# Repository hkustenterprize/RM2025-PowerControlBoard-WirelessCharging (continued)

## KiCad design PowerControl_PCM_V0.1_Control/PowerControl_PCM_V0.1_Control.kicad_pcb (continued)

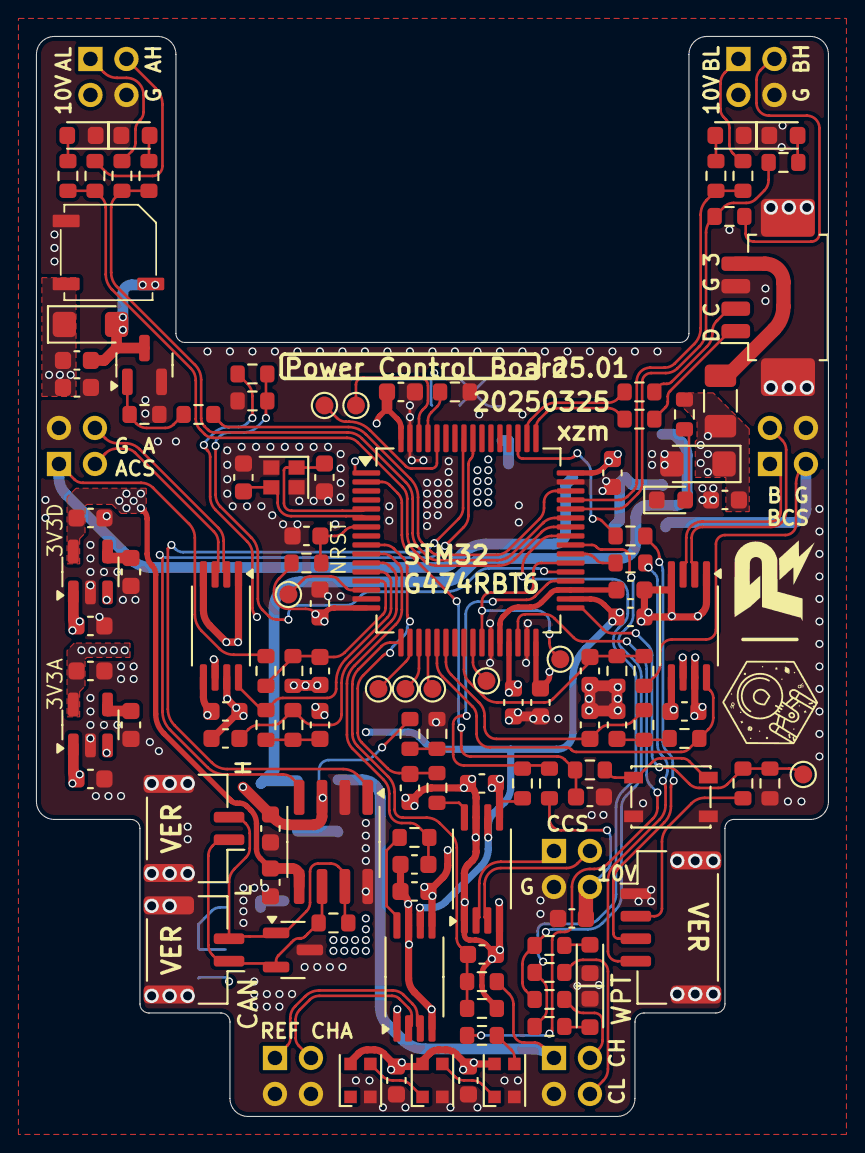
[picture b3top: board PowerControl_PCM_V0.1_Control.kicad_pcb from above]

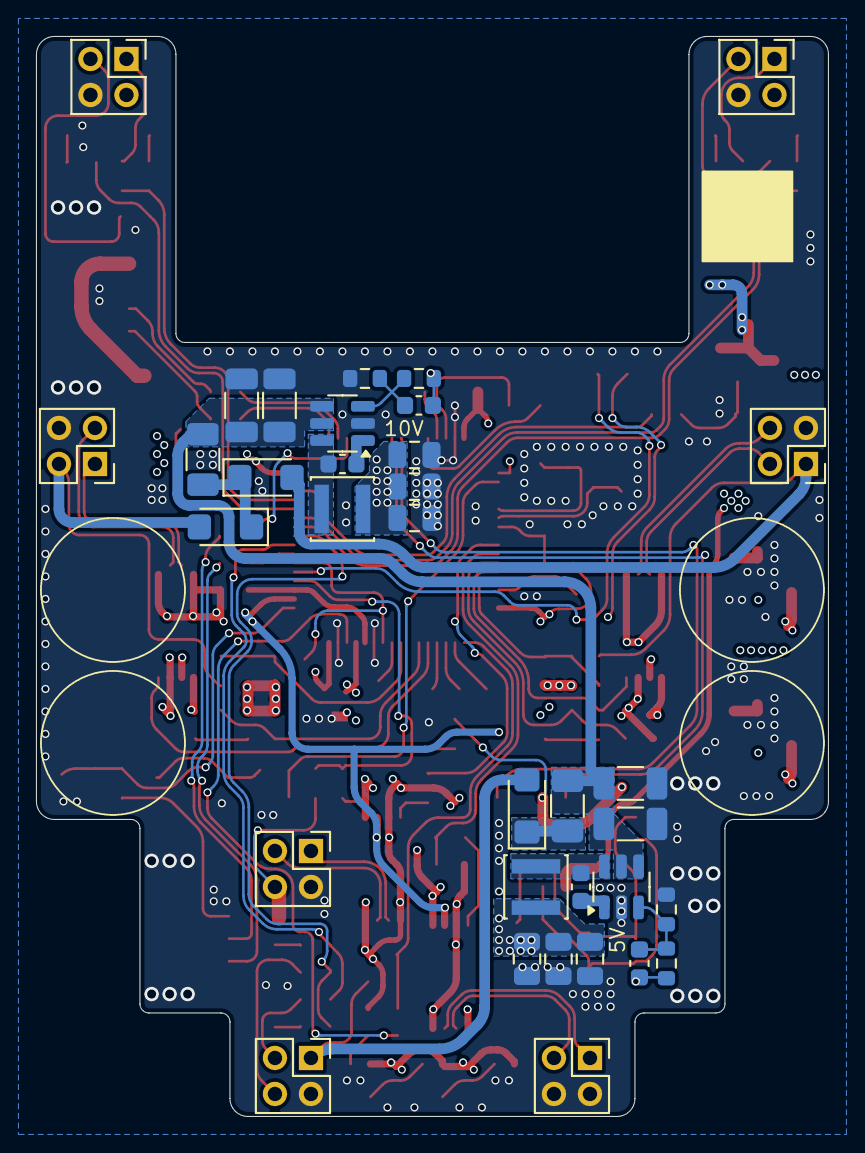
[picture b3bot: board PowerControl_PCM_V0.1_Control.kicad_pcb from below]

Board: 4 copper layers, 44.0 x 60.0 mm, 155 parts (34 on the bottom side), 100 nets.

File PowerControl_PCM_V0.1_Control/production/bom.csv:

Designator,Footprint,Quantity,Value,LCSC Part #
BZ2,Buzzer_5020,1,Buzzer_5020,
"C1, C2, C32, C33, C43, C44, C45, C47, C9",0603,9,3n3,
"C10, C29, C34, C35, C39, C40, C41, C62, C63, C64, C65, C66, C72, C73, C87, C88, C96",0603,17,100n,
"C36, C37, C38, C42, C46, C79",0805,6,22u,
"C48, C49, C50, C74, C85, C86, C90, C94, C95",0603,9,4u7,
"C67, C68, C69, C70",1206,4,10u,
"C75, C77, C78, C89, C91",0603,5,20p,
"C92, C93",0603,2,10n,
D12,SOT-23,1,ESD1CAN,
"D13, D14, D27",WS2812B-2020,3,WS2812B-2020,
D15,0603,1,3V3,
"D18, D21, D7, D8",D_SMF,4,K34,
D19,0603,1,EH,
D20,D_SMF,1,SMF3V3A,
D22,0603,1,AH,
D23,0603,1,AL,
D24,0603,1,BH,
D25,0603,1,BL,
D26,0603,1,EL,
"F4, F5, F6",1206,3,1A 1206,
J1,Molex_PicoBlade_53261-0471_1x04-1MP_P1.25mm_Horizontal,1,SWD,
"J10, J11, J17, J18, J19, J8, J9",PinSocket_2x02_P2.00mm,7,Conn_F,
"J20, J21",JST_GH_BM02B-GHS-TBT_1x02-1MP_P1.25mm_Vertical,2,CAN3,
J22,JST_GH_BM04B-GHS-TBT_1x04-1MP_P1.25mm_Vertical,1,Conn_01x04_MountingPin,
"L1, L4",L_Sunlord_SWPA3015S,2,4u7,
Q11,SOT-23,1,SI2300,
"R1, R40, R43, R45, R47, R48, R49, R50, R51",0603,9,10k,
"R15, R16, R17, R18, R19, R20, R25, R26, R27, R32, R33, R58, R59, R60, R61, R64",0603,16,2k2,
"R21, R28, R29, R30, R31, R39, R41, R46, R52, R53, R54, R55, R57, R62",0603,14,120R,
"R22, R23, R24, R63",0603,4,33k,
"R36, R56",0603,2,1k,
R42,0603,1,118k,
R44,0603,1,53k6,
SW3,Button_PTS810,1,BTN,
TH1,0603,1,Thermistor_NTC,
"TP1, TP2, TP3, TP4, TP5, TP6, TP7, TP8, TP9",TestPoint_Pad_D1.0mm,9,TestPoint,
U12,LQFP-64_10x10mm_P0.5mm,1,STM32G474RBTx,
"U13, U14",SOT-23-6,2,RY8411,
"U16, U17",SOT-23-5,2,RS3236,
"U4, U6, U7, U8",TSSOP-8_4.4x3mm_P0.65mm,4,INA240A1PW,
U5,SOIC-8_3.9x4.9mm_P1.27mm,1,TJA1042T-3,
Y1,Crystal_SMD_2016,1,25Mhz_2016,

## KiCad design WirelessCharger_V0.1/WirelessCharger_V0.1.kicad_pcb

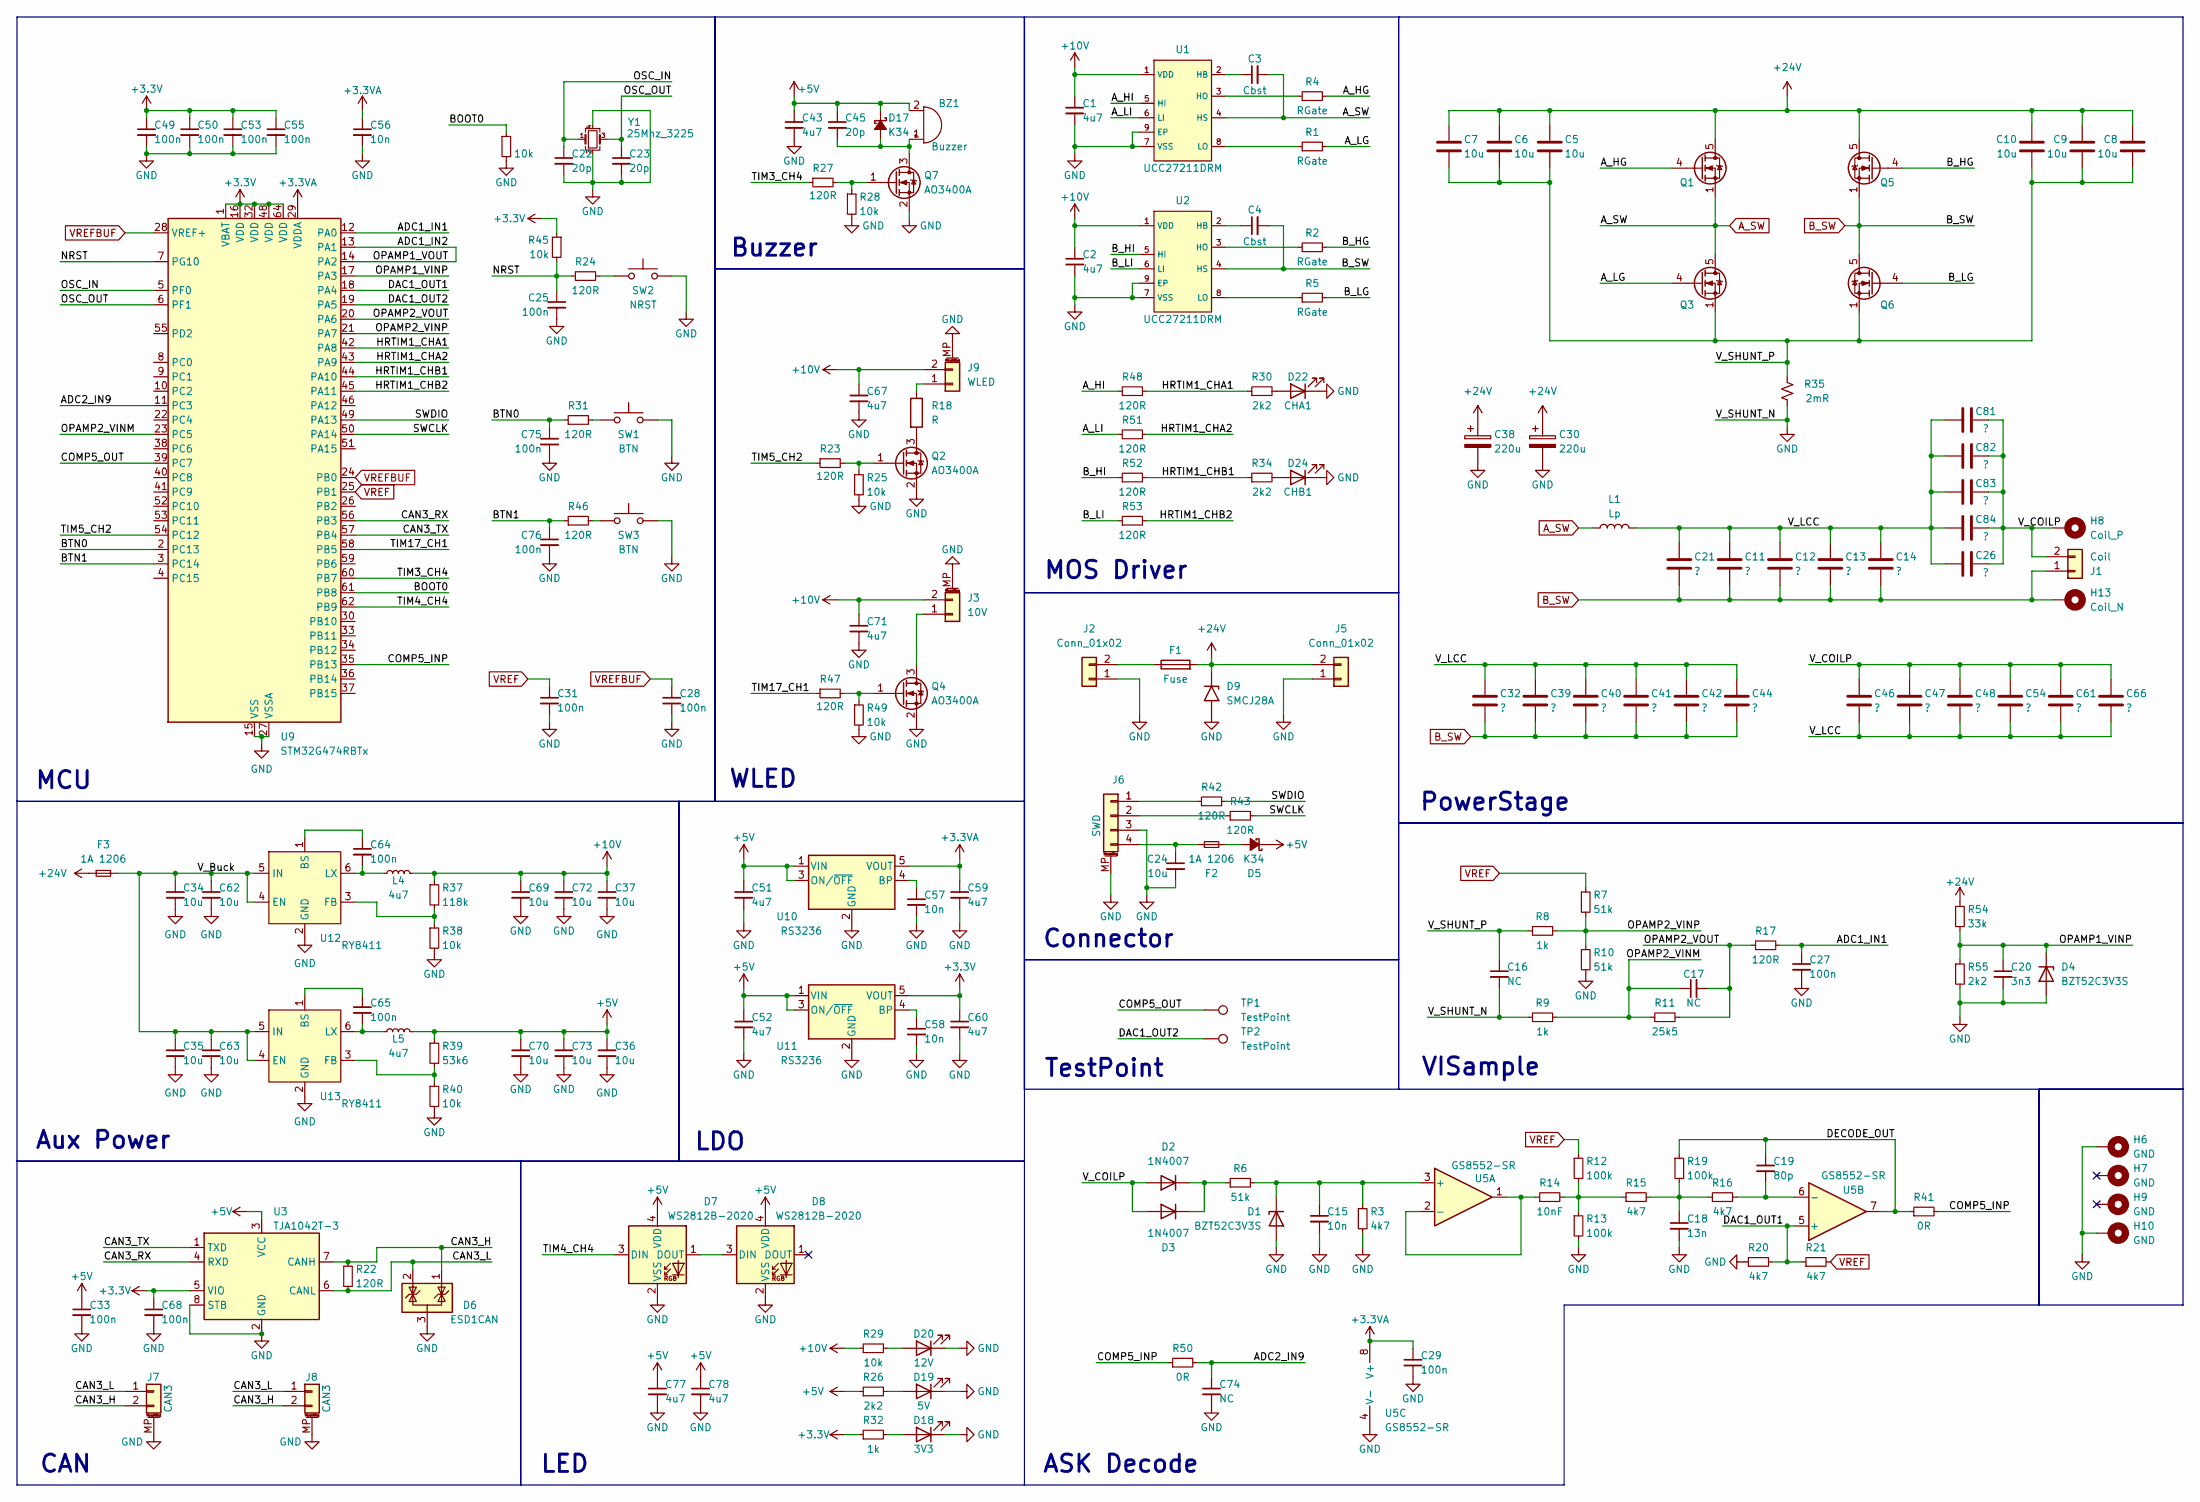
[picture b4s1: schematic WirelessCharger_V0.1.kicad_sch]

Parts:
BZ1: Buzzer; MLT-9032
C1, C2, C43, C51, C52, C59, C60, C67, C71, C77, C78: 4u7; C_0603_1608Metric
C3, C4: Cbst; C_0603_1608Metric
C5, C6, C7, C8, C9, C10, C34, C35, C62, C63: 10u; C_1206_3216Metric
C11, C12, C13, C14, C21, C26, C81, C82, C83, C84: ?; C_Rect_L11.0mm_W5.1mm_P10.00mm_MKT
C15, C56, C57, C58: 10n; C_0603_1608Metric
C16, C17, C74: NC; C_0603_1608Metric
C18: 13n; C_0603_1608Metric
C19: 80p; C_0603_1608Metric
C20: 3n3; C_0603_1608Metric
C22, C23, C45: 20p; C_0603_1608Metric
C24: 10u; C_0603_1608Metric
C25, C27, C28, C29, C31, C33, C49, C50, C53, C55, C64, C65, C68, C75, C76: 100n; C_0603_1608Metric
C30, C38: 220u; CP_Radial_D8.0mm_P3.50mm
C32, C39, C40, C41, C42, C44, C46, C47, C48, C54, C61, C66: ?; C_1206_3216Metric
C36, C37, C69, C70, C72, C73: 10u; C_0805_2012Metric
D1, D4: BZT52C3V3S; D_SOD-123F
D2, D3: 1N4007; D_SMF
D5, D17: K34; D_SMF
D6: ESD1CAN; SOT-23
D7, D8: WS2812B-2020
D9: SMCJ28A; D_SMC
D18: 3V3; LED_0603_1608Metric
D19: 5V; LED_0603_1608Metric
D20: 12V; LED_0603_1608Metric
D22: CHA1; LED_0603_1608Metric
D24: CHB1; LED_0603_1608Metric
F1: Fuse; Fuse_Littelfuse-NANO2-451_453
F2, F3: 1A 1206; Fuse_1206_3216Metric
H6, H7, H9, H10: GND; MountingHole_3.2mm_M3_DIN965_Pad
H8: Coil_P; TestPoint_Plated_Hole_D2.0mm
H13: Coil_N; TestPoint_Plated_Hole_D2.0mm
J1: Coil; AMASS_XT30U-F_Vertical
J2: Conn_01x02; AMASS_XT30U-M_Vertical
J3: 10V; JST_PH_B2B-PH-SM4-TB_1x02-1MP_P2.00mm_Vertical
J5: Conn_01x02; AMASS_XT30U-F_Vertical
J6: SWD; Molex_PicoBlade_53261-0471_1x04-1MP_P1.25mm_Horizontal
J7, J8: CAN3; JST_GH_BM02B-GHS-TBT_1x02-1MP_P1.25mm_Vertical
J9: WLED; JST_PH_B2B-PH-SM4-TB_1x02-1MP_P2.00mm_Vertical
L1: Lp; L_90125_3P
L4, L5: 4u7; L_Sunlord_SWPA3015S
Q1, Q3, Q5, Q6: BSC070N10NS3G; TDSON-8-1
Q2, Q4, Q7: AO3400A; SOT-23
R1, R2, R4, R5: RGate; R_0603_1608Metric
R3, R15, R16, R20, R21: 4k7; R_0603_1608Metric
R6, R7, R10: 51k; R_0603_1608Metric
R8, R9, R32: 1k; R_0603_1608Metric
R11: 25k5; R_0603_1608Metric
R12, R13, R19: 100k; R_0603_1608Metric
R14: 10nF; R_0603_1608Metric
R17, R22, R23, R24, R27, R31, R42, R43, R46, R47, R48, R51, R52, R53: 120R; R_0603_1608Metric
R18: R; R_1206_3216Metric
R25, R28, R29, R38, R40, R44, R45, R49: 10k; R_0603_1608Metric
R26, R30, R34, R55: 2k2; R_0603_1608Metric
R35: 2mR; R_2512_6332Metric
R37: 118k; R_0603_1608Metric
R39: 53k6; R_0603_1608Metric
R41, R50: 0R; R_0603_1608Metric
R54: 33k; R_0603_1608Metric
SW1, SW3: BTN; Button_PTS810
SW2: NRST; Button_PTS810
TP1, TP2: TestPoint; TestPoint_Pad_D1.5mm
U1, U2: UCC27211DRM; SOIC-8_3.9x4.9mm_P1.27mm
U3: TJA1042T-3; SOIC-8_3.9x4.9mm_P1.27mm
U5: GS8552-SR; SOIC-8_3.9x4.9mm_P1.27mm
U9: STM32G474RBTx; LQFP-64_10x10mm_P0.5mm
U10, U11: RS3236; SOT-23-5
U12, U13: RY8411; SOT-23-6
Y1: 25Mhz_3225; Crystal_SMD_2016

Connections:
+3.3V: C49.1, C50.1, C53.1, C55.1, C60.1, C68.1, R32.1, R45.1, U3.5 (VIO), U9.1 (VBAT), U9.16 (VDD), U9.32 (VDD), U9.48 (VDD), U9.64 (VDD), U11.5 (VOUT)
+3.3VA: C29.1, C56.1, C59.1, U5.8 (V+), U9.29 (VDDA), U10.5 (VOUT)
+5V: BZ1.2 (+), C33.1, C36.1, C43.1, C45.1, C51.1, C52.1, C70.1, C73.1, C77.1, C78.1, D5.1 (K), D7.4 (VDD), D8.4 (VDD), D17.1 (K), L5.2, R26.1, R39.1, U3.3 (VCC), U10.1 (VIN), U10.3 (ON/~OFF), U11.1 (VIN), U11.3 (ON/~OFF)
+10V: C1.1, C2.1, C37.1, C67.1, C69.1, C71.1, C72.1, J3.2, J9.2, L4.2, R29.1, R37.1, U1.1 (VDD), U2.1 (VDD)
+24V: C5.1, C6.1, C7.1, C8.1, C9.1, C10.1, C30.1, C38.1, D9.1 (A1), F1.2, F3.1, J5.2, Q1.5 (D), Q5.5 (D), R54.1
/ADC1_IN1: C27.1, R17.2, U9.12 (PA0)
/ADC1_IN2: U9.13 (PA1), U9.14 (PA2)
/ADC2_IN9: C74.1, R50.2, U9.11 (PC3)
/A_HG: Q1.4 (G), R4.2
/A_HI: R48.1, U1.5 (HI)
/A_LG: Q3.4 (G), R1.2
/A_LI: R51.1, U1.6 (LI)
/BOOT0: R44.1, U9.61 (PB8)
/BTN0: C75.1, R31.1, U9.2 (PC13)
/BTN1: C76.1, R46.1, U9.3 (PC14)
/B_HG: Q5.4 (G), R2.2
/B_HI: R52.1, U2.5 (HI)
/B_LG: Q6.4 (G), R5.2
/B_LI: R53.1, U2.6 (LI)
/CAN3_H: D6.1 (K), J7.2, J8.2, R22.1, U3.7 (CANH)
/CAN3_L: D6.2 (K), J7.1, J8.1, R22.2, U3.6 (CANL)
/CAN3_RX: U3.4 (RXD), U9.56 (PB3)
/CAN3_TX: U3.1 (TXD), U9.57 (PB4)
/COMP5_INP: R41.2, R50.1, U9.35 (PB13)
/COMP5_OUT: TP1.1, U9.39 (PC7)
/DAC1_OUT1: R20.2, R21.1, U5.5 (+), U9.18 (PA4)
/DAC1_OUT2: TP2.1, U9.19 (PA5)
/DECODE_OUT: C19.1, R19.1, R41.1, U5.7
/HRTIM1_CHA1: R30.1, R48.2, U9.42 (PA8)
/HRTIM1_CHA2: R51.2, U9.43 (PA9)
/HRTIM1_CHB1: R34.1, R52.2, U9.44 (PA10)
/HRTIM1_CHB2: R53.2, U9.45 (PA11)
/NRST: C25.1, R24.1, R45.2, U9.7 (PG10)
/OPAMP1_VINP: C20.1, D4.1 (K), R54.2, R55.1, U9.17 (PA3)
/OPAMP2_VINM: C17.1, R9.2, R11.1, U9.23 (PC5)
/OPAMP2_VINP: R7.2, R8.2, R10.1, U9.21 (PA7)
/OPAMP2_VOUT: C17.2, R11.2, R17.1, U9.20 (PA6)
/OSC_IN: C22.1, U9.5 (PF0), Y1.1
/OSC_OUT: C23.1, U9.6 (PF1), Y1.3
/SWCLK: R43.2, U9.50 (PA14)
/SWDIO: R42.2, U9.49 (PA13)
/TIM3_CH4: R27.1, U9.60 (PB7)
/TIM4_CH4: D7.3 (DIN), U9.62 (PB9)
/TIM5_CH2: R23.1, U9.54 (PC12)
/TIM17_CH1: R47.1, U9.58 (PB5)
/V_Buck: C34.1, C35.1, C62.1, C63.1, F3.2, U12.4 (EN), U12.5 (IN), U13.4 (EN), U13.5 (IN)
/V_COILP: C26.2, C46.1, C47.1, C48.1, C54.1, C61.1, C66.1, C81.2, C82.2, C83.2, C84.2, D2.2 (A), D3.2 (A), H8.1, J1.2
/V_LCC: C11.1, C12.1, C13.1, C14.1, C21.1, C26.1, C32.1, C39.1, C40.1, C41.1, C42.1, C44.1, C46.2, C47.2, C48.2, C54.2, C61.2, C66.2, C81.1, C82.1, C83.1, C84.1, L1.1
/V_SHUNT_P: C5.2, C6.2, C7.2, C8.2, C9.2, C10.2, C16.1, Q3.1 (S), Q3.2 (S), Q3.3 (S), Q6.1 (S), Q6.2 (S), Q6.3 (S), R8.1, R35.2
A_SW: C3.2, L1.2, Q1.1 (S), Q1.2 (S), Q1.3 (S), Q3.5 (D), U1.4 (HS)
B_SW: C4.2, C11.2, C12.2, C13.2, C14.2, C21.2, C32.2, C39.2, C40.2, C41.2, C42.2, C44.2, H13.1, J1.1, Q5.1 (S), Q5.2 (S), Q5.3 (S), Q6.5 (D), U2.4 (HS)
GND: C1.2, C2.2, C15.2, C16.2, C18.2, C20.2, C22.2, C23.2, C24.2, C25.2, C27.2, C28.2, C29.2, C30.2, C31.2, C33.2, C34.2, C35.2, C36.2, C37.2, C38.2, C43.2, C49.2, C50.2, C51.2, C52.2, C53.2, C55.2, C56.2, C57.2, C58.2, C59.2, C60.2, C62.2, C63.2, C67.2, C68.2, C69.2, C70.2, C71.2, C72.2, C73.2, C74.2, C75.2, C76.2, C77.2, C78.2, D1.2 (A), D4.2 (A), D6.3 (A), D7.2 (VSS), D8.2 (VSS), D9.2 (A2), D18.1 (K), D19.1 (K), D20.1 (K), D22.1 (K), D24.1 (K), H6.1, H10.1, J2.1, J3.MP (MountPin), J5.1, J6.3, J6.MP (MountPin), J7.MP (MountPin), J8.MP (MountPin), J9.MP (MountPin), Q2.2 (S), Q4.2 (S), Q7.2 (S), R3.2, R9.1, R10.2, R13.2, R20.1, R25.2, R28.2, R35.1, R38.2, R40.2, R44.2, R49.2, R55.2, SW1.2, SW2.2, SW3.2, U1.7 (VSS), U1.9 (EP), U2.7 (VSS), U2.9 (EP), U3.2 (GND), U3.8 (STB), U5.4 (V-), U9.15 (VSS), U9.27 (VSSA), U9.31 (VSS), U9.47 (VSS), U9.63 (VSS), U10.2 (GND), U11.2 (GND), U12.2 (GND), U13.2 (GND), Y1.2, Y1.4
unnamed: BZ1.1 (-), C45.2, D17.2 (A), Q7.3 (D)
unnamed: C18.1, R15.2, R16.1, R19.2
unnamed: C15.1, D1.1 (K), R3.1, R6.2, U5.3 (+)
unnamed: D2.1 (K), D3.1 (K), R6.1
unnamed: D5.2 (A), F2.2
unnamed: D7.1 (DOUT), D8.3 (DIN)
unnamed: D18.2 (A), R32.2
unnamed: D19.2 (A), R26.2
unnamed: D20.2 (A), R29.2
unnamed: D22.2 (A), R30.2
unnamed: D24.2 (A), R34.2
unnamed: F1.1, J2.2
unnamed: J3.1, Q4.3 (D)
unnamed: J6.1, R42.1
unnamed: J6.2, R43.1
unnamed: C24.1, F2.1, J6.4
unnamed: J9.1, R18.1
unnamed: Q2.3 (D), R18.2
unnamed: Q2.1 (G), R23.2, R25.1
unnamed: Q4.1 (G), R47.2, R49.1
unnamed: Q7.1 (G), R27.2, R28.1
unnamed: R12.2, R13.1, R14.2, R15.1
unnamed: R24.2, SW2.1
unnamed: R31.2, SW1.1
unnamed: R46.2, SW3.1
unnamed: C3.1, U1.2 (HB)
unnamed: R4.1, U1.3 (HO)
unnamed: R1.1, U1.8 (LO)
unnamed: C4.1, U2.2 (HB)
unnamed: R2.1, U2.3 (HO)
unnamed: R5.1, U2.8 (LO)
unnamed: R14.1, U5.1, U5.2 (-)
unnamed: C19.2, R16.2, U5.6 (-)
unnamed: C57.1, U10.4 (BP)
unnamed: C58.1, U11.4 (BP)
unnamed: C64.1, U12.1 (BS)
unnamed: R37.2, R38.1, U12.3 (FB)
unnamed: C64.2, L4.1, U12.6 (LX)
unnamed: C65.1, U13.1 (BS)
unnamed: R39.2, R40.1, U13.3 (FB)
unnamed: C65.2, L5.1, U13.6 (LX)
VREF: C31.1, R7.1, R12.1, R21.2, U9.25 (PB1)
VREFBUF: C28.1, U9.24 (PB0), U9.28 (VREF+)

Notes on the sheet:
VISample
TestPoint
LED
Aux Power
PowerStage
MCU
Connector
WLED
Buzzer
LDO
ASK Decode
MOS Driver
CAN

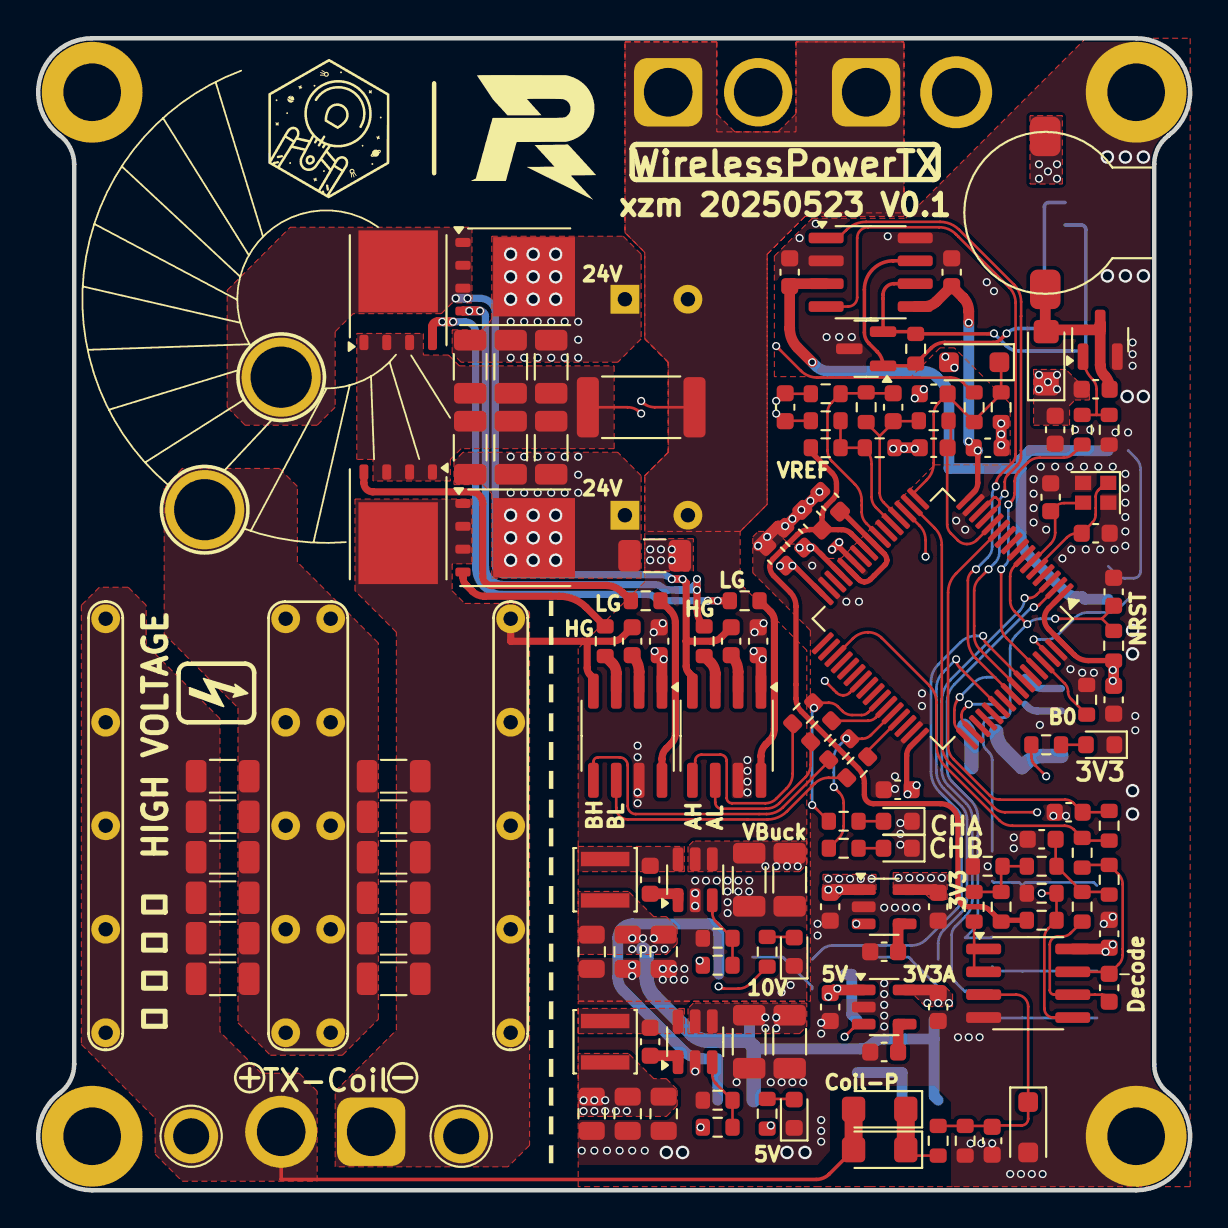
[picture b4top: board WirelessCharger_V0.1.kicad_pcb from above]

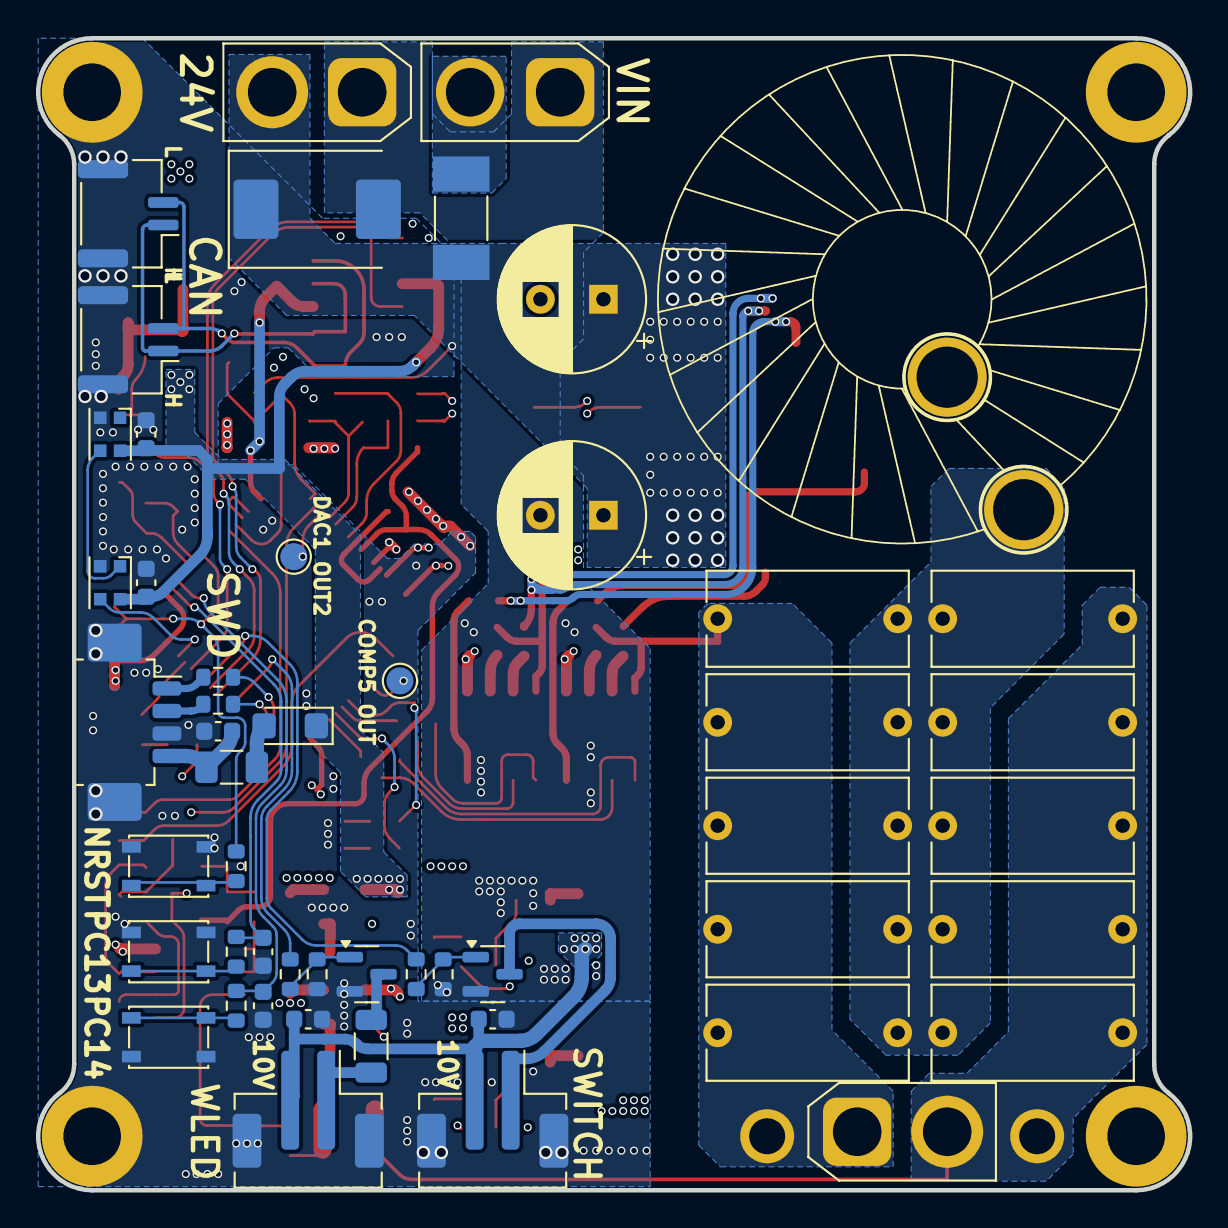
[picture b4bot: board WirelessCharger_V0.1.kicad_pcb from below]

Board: 4 copper layers, 64.0 x 64.0 mm, 193 parts (51 on the bottom side), 95 nets.

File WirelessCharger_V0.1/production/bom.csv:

Designator,Footprint,Quantity,Value,LCSC Part #
BZ1,MLT-9032,1,Buzzer,
"C1, C2, C43, C51, C52, C59, C60, C67, C71, C77, C78",0603,11,4u7,
"C10, C34, C35, C5, C6, C62, C63, C7, C8, C9",1206,10,10u,
"C11, C12, C13, C14, C21, C26, C81, C82, C83, C84",C_Rect_L11.0mm_W5.1mm_P10.00mm_MKT,10,?,
"C15, C56, C57, C58",0603,4,10n,
"C16, C17, C74",0603,3,NC,
C18,0603,1,13n,
C19,0603,1,80p,
C20,0603,1,3n3,
"C22, C23, C45",0603,3,20p,
C24,0603,1,10u,
"C25, C27, C28, C29, C31, C33, C49, C50, C53, C55, C64, C65, C68, C75, C76",0603,15,100n,
"C3, C4",0603,2,Cbst,
"C30, C38",CP_Radial_D8.0mm_P3.50mm,2,220u,
"C32, C39, C40, C41, C42, C44, C46, C47, C48, C54, C61, C66",1206,12,?,
"C36, C37, C69, C70, C72, C73",0805,6,10u,
"D1, D4",D_SOD-123F,2,BZT52C3V3S,
"D17, D5",D_SMF,2,K34,
D18,0603,1,3V3,
D19,0603,1,5V,
"D2, D3",D_SMF,2,1N4007,
D20,0603,1,12V,
D22,0603,1,CHA1,
D24,0603,1,CHB1,
D6,SOT-23,1,ESD1CAN,
"D7, D8",WS2812B-2020,2,WS2812B-2020,
D9,D_SMC,1,SMCJ28A,
F1,Fuse_Littelfuse-NANO2-451_453,1,Fuse,
"F2, F3",1206,2,1A 1206,
"H10, H6, H7, H9",MountingHole_3.2mm_M3_DIN965_Pad,4,GND,
H13,TestPoint_Plated_Hole_D2.0mm,1,Coil_N,
H8,TestPoint_Plated_Hole_D2.0mm,1,Coil_P,
J1,AMASS_XT30U-F_Vertical,1,Coil,
J2,AMASS_XT30U-M_Vertical,1,Conn_01x02,
J3,JST_PH_B2B-PH-SM4-TB_1x02-1MP_P2.00mm_Vertical,1,10V,
J5,AMASS_XT30U-F_Vertical,1,Conn_01x02,
J6,Molex_PicoBlade_53261-0471_1x04-1MP_P1.25mm_Horizontal,1,SWD,
"J7, J8",JST_GH_BM02B-GHS-TBT_1x02-1MP_P1.25mm_Vertical,2,CAN3,
J9,JST_PH_B2B-PH-SM4-TB_1x02-1MP_P2.00mm_Vertical,1,WLED,
L1,L_90125_3P,1,Lp,
"L4, L5",L_Sunlord_SWPA3015S,2,4u7,
"Q1, Q3, Q5, Q6",TDSON-8-1,4,BSC070N10NS3G,
"Q2, Q4, Q7",SOT-23,3,AO3400A,
"R1, R2, R4, R5",0603,4,RGate,
"R10, R6, R7",0603,3,51k,
R11,0603,1,25k5,
"R12, R13, R19",0603,3,100k,
R14,0603,1,10nF,
"R15, R16, R20, R21, R3",0603,5,4k7,
"R17, R22, R23, R24, R27, R31, R42, R43, R46, R47, R48, R51, R52, R53",0603,14,120R,
R18,1206,1,R,
"R25, R28, R29, R38, R40, R44, R45, R49",0603,8,10k,
"R26, R30, R34, R55",0603,4,2k2,
"R32, R8, R9",0603,3,1k,
R35,2512,1,2mR,
R37,0603,1,118k,
R39,0603,1,53k6,
"R41, R50",0603,2,0R,
R54,0603,1,33k,
"SW1, SW3",Button_PTS810,2,BTN,
SW2,Button_PTS810,1,NRST,
"TP1, TP2",TestPoint_Pad_D1.5mm,2,TestPoint,
"U1, U2",SOIC-8_3.9x4.9mm_P1.27mm,2,UCC27211DRM,
"U10, U11",SOT-23-5,2,RS3236,
"U12, U13",SOT-23-6,2,RY8411,
U3,SOIC-8_3.9x4.9mm_P1.27mm,1,TJA1042T-3,
U5,SOIC-8_3.9x4.9mm_P1.27mm,1,GS8552-SR,
U9,LQFP-64_10x10mm_P0.5mm,1,STM32G474RBTx,
Y1,Crystal_SMD_2016,1,25Mhz_3225,

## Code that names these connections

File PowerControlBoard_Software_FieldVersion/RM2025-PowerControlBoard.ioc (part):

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Mcu.Name=STM32G474R(B-C-E)Tx
Mcu.Package=LQFP64
Mcu.UserName=STM32G474RBTx
PA0.Mode=INP
PA0.Signal=COMP3_INP
PA1.Mode=Follower
PA1.Signal=OPAMP3_VINP
PA10.Mode=Output_TB1TB2
PA10.Signal=HRTIM1_CHB1
PA11.Mode=Output_TB1TB2
PA11.Signal=HRTIM1_CHB2
PA12.Mode=PWM Generation2 CH2N
PA12.Signal=TIM1_CH2N
PA13.Mode=Serial_Wire
PA13.Signal=SYS_JTMS-SWDIO
PA14.Mode=Serial_Wire
PA14.Signal=SYS_JTCK-SWCLK
PA15.GPIOParameters=GPIO_Speed,GPIO_Label
PA15.GPIO_Label=COMM1
PA15.GPIO_Speed=GPIO_SPEED_FREQ_VERY_HIGH
PA15.Signal=GPIO_Output
PA2.Signal=SharedAnalog_PA2
PA3.Mode=Follower
PA3.Signal=OPAMP1_VINP
PA4.Signal=COMP_DAC11_group
PA5.Signal=COMP_DAC12_group
PA6.Signal=SharedAnalog_PA6
PA7.Mode=INP
PA7.Signal=COMP2_INP
PA8.Mode=Output_TA1TA2
PA8.Signal=HRTIM1_CHA1
PA9.Mode=Output_TA1TA2
PA9.Signal=HRTIM1_CHA2
PB0.Mode=Follower
PB0.Signal=OPAMP2_VINP
PB1.Signal=SharedAnalog_PB1
PB10.Signal=S_TIM2_CH3
PB11.Mode=INP
PB11.Signal=COMP6_INP
PB12.Mode=Follower
PB12.Signal=OPAMP4_VOUT
PB13.Mode=Follower
PB13.Signal=OPAMP4_VINP
PB14.Mode=IN4-Single-Ended
PB14.Signal=ADC4_IN4
PB15.Mode=IN5-Single-Ended
PB15.Signal=ADC4_IN5
PB2.Signal=S_TIM5_CH1
PB3.Mode=FDCAN_Activate
PB3.Signal=FDCAN3_RX
PB4.Mode=FDCAN_Activate
PB4.Signal=FDCAN3_TX
PB7.Mode=ExternalOutput
PB7.Signal=COMP3_OUT
PB9.GPIOParameters=GPIO_Speed,GPIO_FM9
PB9.GPIO_FM9=__NULL
PB9.GPIO_Speed=GPIO_SPEED_FREQ_LOW
PB9.Mode=ExternalOutput
PB9.Signal=COMP2_OUT
PC1.Mode=IN7-Single-Ended
PC1.Signal=ADC2_IN7
PC13.GPIOParameters=GPIO_PuPd,GPIO_Label
PC13.GPIO_Label=BTN
PC13.GPIO_PuPd=GPIO_PULLUP
PC13.Signal=GPIO_Input
PC2.Mode=IN8-Single-Ended
PC2.Signal=ADC1_IN8
PC3.Mode=IN9-Single-Ended
PC3.Signal=ADC1_IN9
PC4.Mode=IN5-Single-Ended
PC4.Signal=ADC2_IN5
PC6.Mode=ExternalOutput
PC6.Signal=COMP6_OUT
PC7.GPIOParameters=GPIO_Label
PC7.GPIO_Label=COMM2
PC7.Signal=GPIO_Output
PC8.Mode=Output_TE1TE2
PC8.Signal=HRTIM1_CHE1
PC9.Mode=Output_TE1TE2
PC9.Signal=HRTIM1_CHE2
PF0-OSC_IN.Mode=HSE-External-Oscillator
PF0-OSC_IN.Signal=RCC_OSC_IN
PF1-OSC_OUT.Mode=HSE-External-Oscillator
PF1-OSC_OUT.Signal=RCC_OSC_OUT
RCC.HSE_VALUE=25000000
RCC.SYSCLKFreq_VALUE=170000000
RCC.SYSCLKSource=RCC_SYSCLKSOURCE_PLLCLK
board=custom

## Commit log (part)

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2025-08-08 外壳文件
2025-08-09 更新技术报告
2025-08-22 更新readme
2025-08-24 更新上场版代码
2025-08-24 更新Calibration
2025-10-06 增加校准excel
2025-11-24 feat:add docker build
